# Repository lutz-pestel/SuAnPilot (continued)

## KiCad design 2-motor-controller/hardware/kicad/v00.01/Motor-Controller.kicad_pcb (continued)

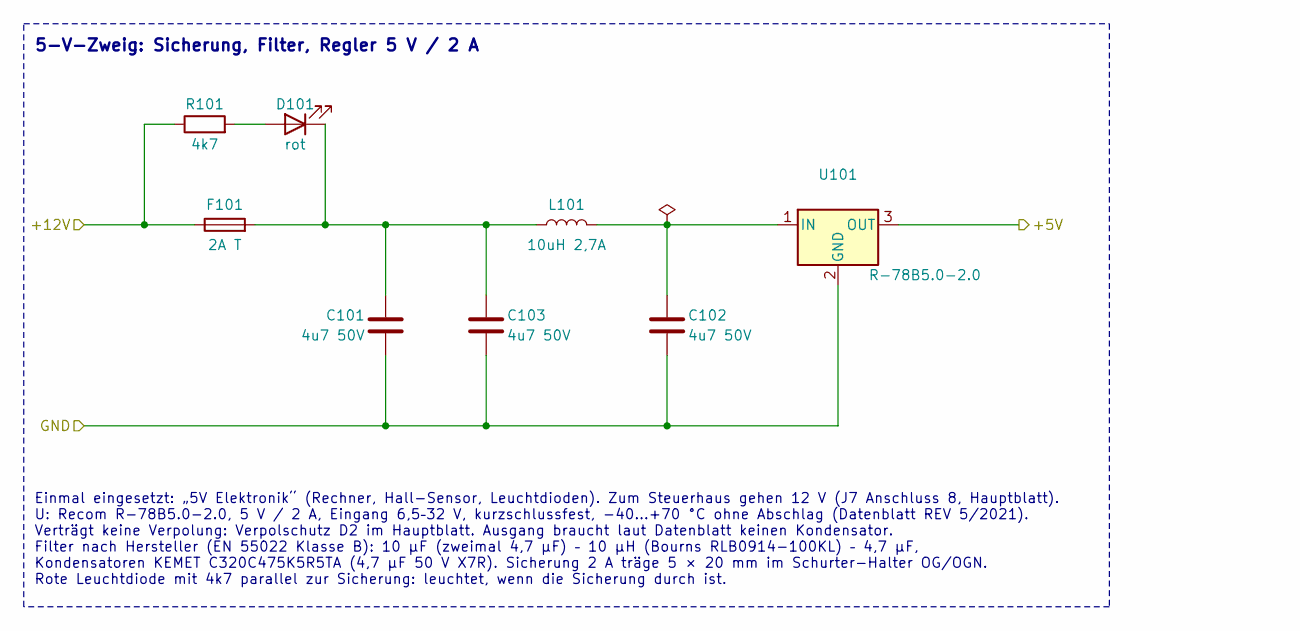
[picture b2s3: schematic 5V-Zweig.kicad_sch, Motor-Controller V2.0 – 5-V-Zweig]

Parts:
C101, C102, C103: 4u7 50V; C_KEMET_C320_L5.1mm_W4.1mm_P2.54mm
D101: rot; LED_Dialight_551_RightAngle
F101: 2A T; Fuseholder_Cylinder-5x20mm_Schurter_0031_8201_Horizontal_Op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
L101: 10uH 2,7A; L_Radial_D10.0mm_P5.00mm_Fastron_07P
R101: 4k7; R_Axial_DIN0207_L6.3mm_D2.5mm_P10.16mm_Horizontal
U101: R-78B5.0-2.0; Converter_DCDC_RECOM_R-78B-2.0_THT

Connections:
+5V: U101.3 (OUT); also elsewhere on the board
+12V: F101.1, R101.1; also elsewhere on the board
GND: C101.2, C102.2, C103.2, U101.2 (GND); also elsewhere on the board
unnamed: D101.2 (A), R101.2
unnamed: C101.1, C103.1, D101.1 (K), F101.2, L101.1
unnamed: C102.1, L101.2, U101.1 (IN)

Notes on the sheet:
5-V-Zweig: Sicherung, Filter, Regler 5 V / 2 A
Einmal eingesetzt: „5V Elektronik“ (Rechner, Hall-Sensor, Leuchtdioden). Zum Steuerhaus gehen 12 V (J7 Anschluss 8, Hauptblatt). U: Recom R-78B5.0-2.0, 5 V / 2 A, Eingang 6,5–32 V, kurzschlussfest, −40…+70 °C ohne Abschlag (Datenblatt REV 5/2021). Verträgt keine Verpolung: Verpolschutz D2 im Hauptb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

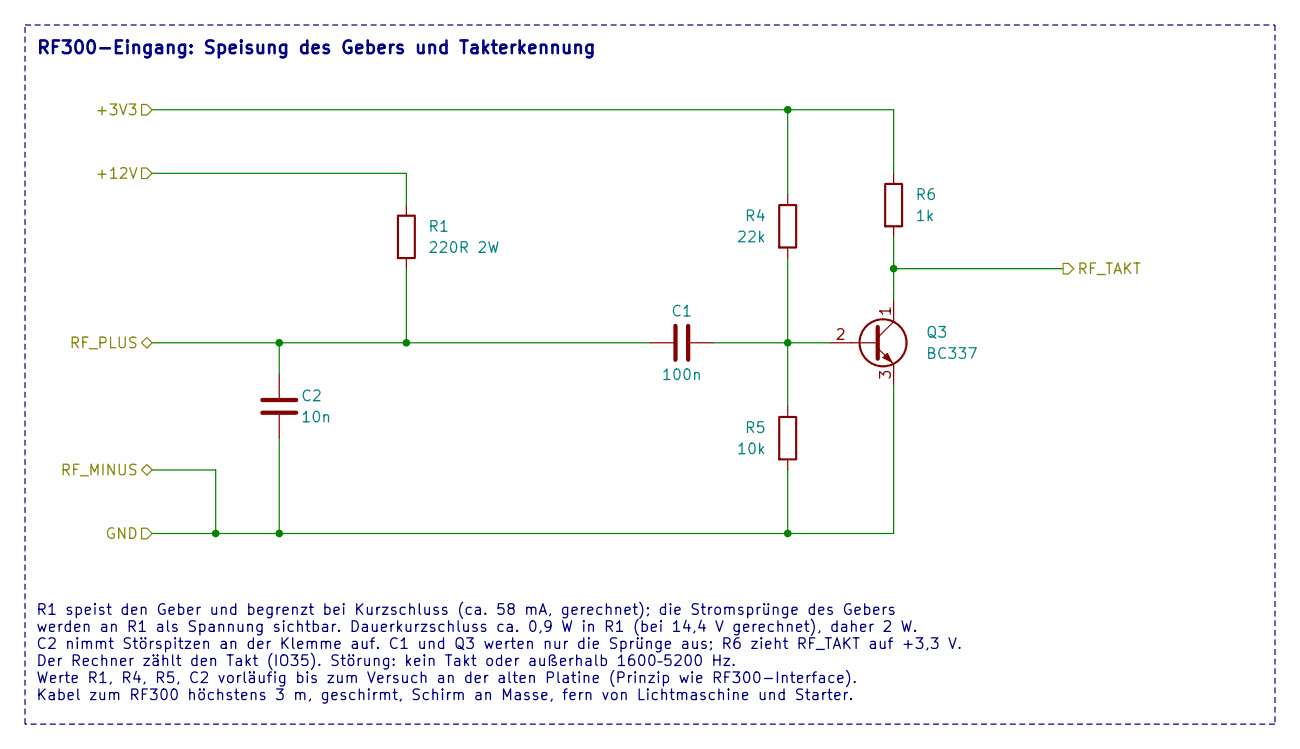
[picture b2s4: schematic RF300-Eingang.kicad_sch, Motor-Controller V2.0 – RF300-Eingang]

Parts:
C1: 100n; C_KEMET_C320_L5.1mm_W4.1mm_P2.54mm
C2: 10n; C_KEMET_C320_L5.1mm_W4.1mm_P2.54mm
Q3: BC337; TO-92_Inline
R1: 220R 2W; R_Axial_DIN0617_L17.0mm_D6.0mm_P20.32mm_Horizontal
R4: 22k; R_Axial_DIN0207_L6.3mm_D2.5mm_P10.16mm_Horizontal
R5: 10k; R_Axial_DIN0207_L6.3mm_D2.5mm_P10.16mm_Horizontal
R6: 1k; R_Axial_DIN0207_L6.3mm_D2.5mm_P10.16mm_Horizontal

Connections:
+3V3: R4.1, R6.1; also elsewhere on the board
+12V: R1.1; also elsewhere on the board
/RF300-Eingang/RF_PLUS: C1.1, C2.1, R1.2; also elsewhere on the board
/RF_TAKT: Q3.1 (C), R6.2; also elsewhere on the board
GND: C2.2, Q3.3 (E), R5.2; also elsewhere on the board
unnamed: C1.2, Q3.2 (B), R4.2, R5.1

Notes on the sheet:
RF300-Eingang: Speisung des Gebers und Takterkennung
R1 speist den Geber und begrenzt bei Kurzschluss (ca. 58 mA, gerechnet); die Stromsprünge des Gebers werden an R1 als Spannung sichtbar. Dauerkurzschluss ca. 0,9 W in R1 (bei 14,4 V gerechnet), daher 2 W. C2 nimmt Störspitzen an der Klemme auf. C1 und Q3 werten nur die Sprünge aus; R6 zieht RF_TAKT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

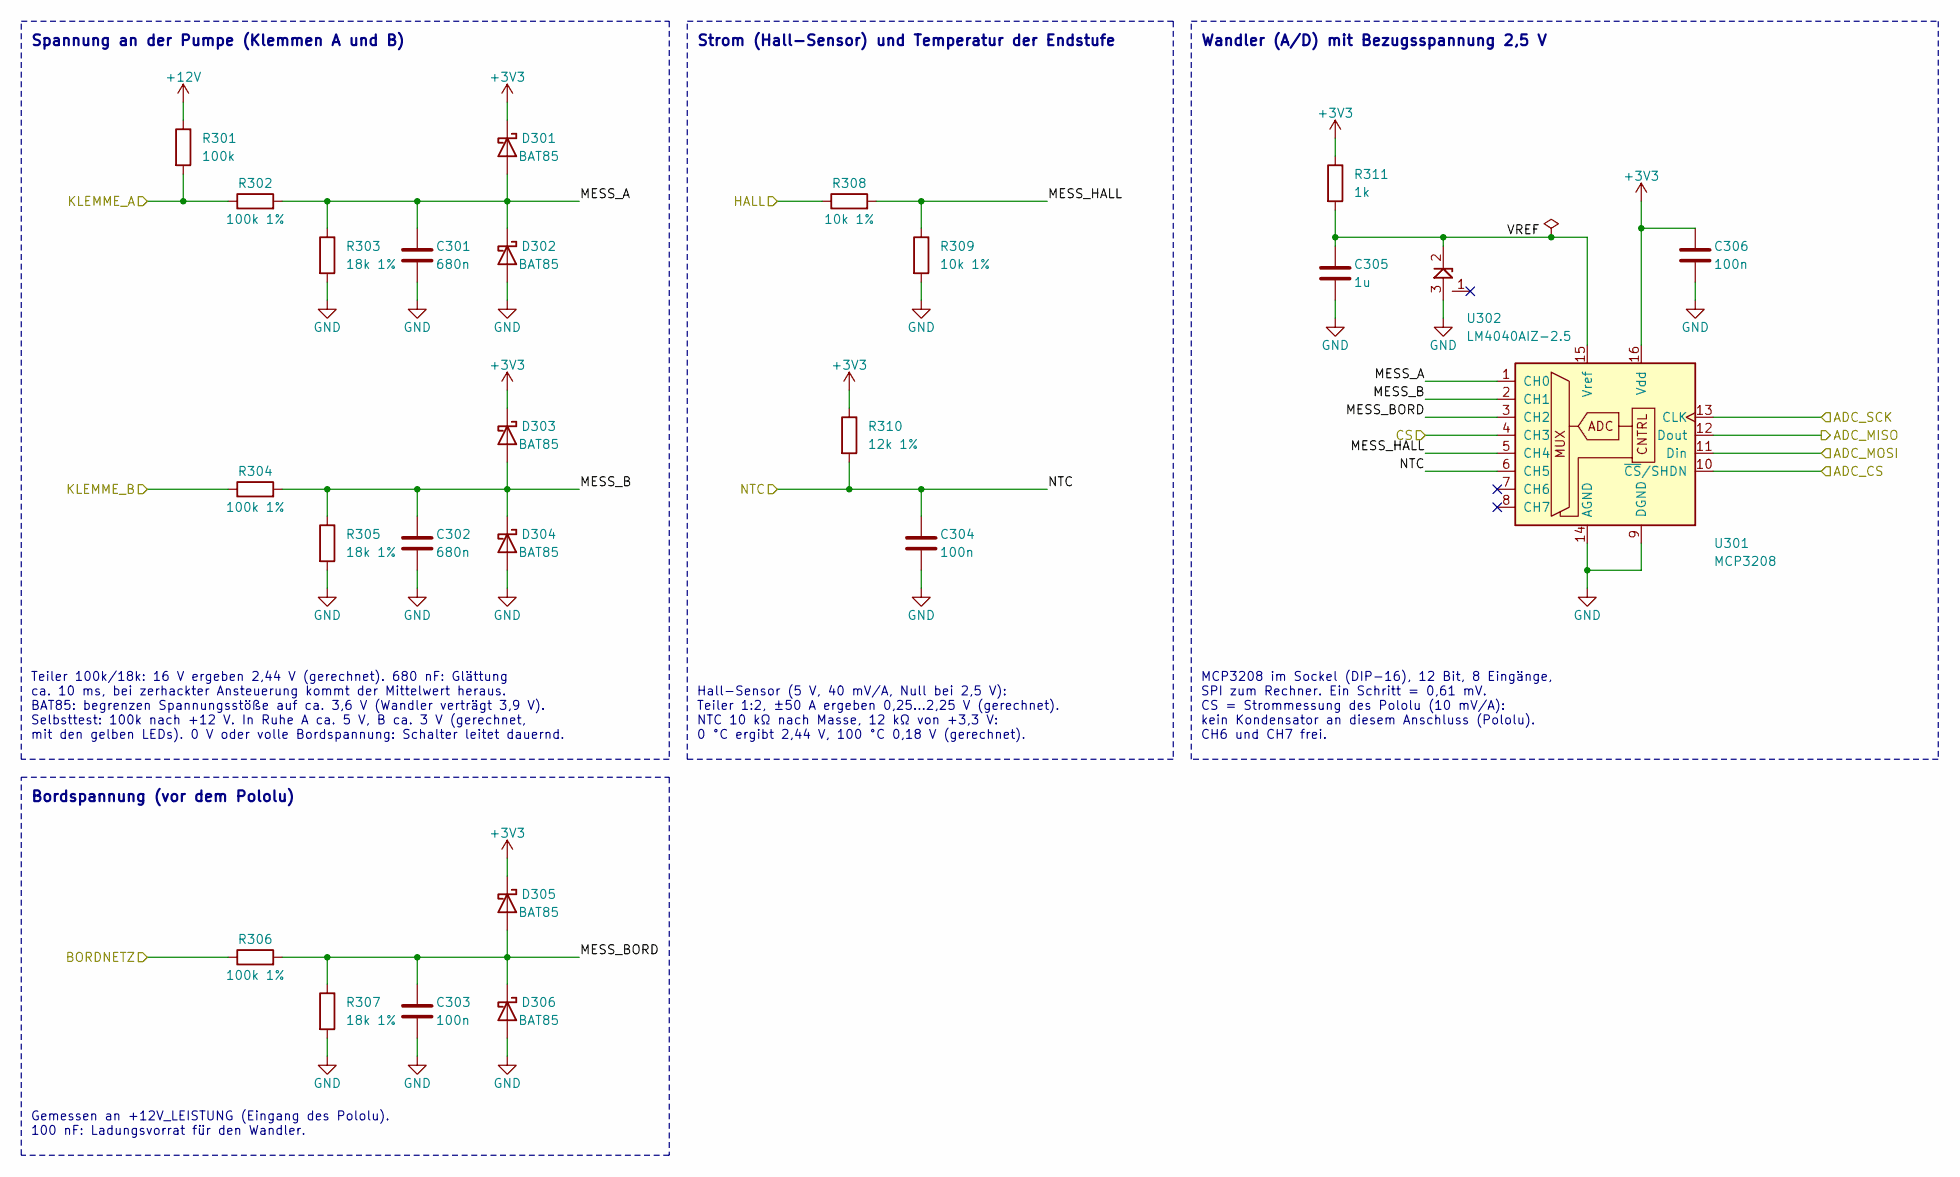
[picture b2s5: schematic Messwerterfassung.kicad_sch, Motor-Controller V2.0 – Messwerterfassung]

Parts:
C301, C302: 680n; C_KEMET_C320_L5.1mm_W4.1mm_P2.54mm
C303, C304, C306: 100n; C_KEMET_C320_L5.1mm_W4.1mm_P2.54mm
C305: 1u; C_Rect_L7.2mm_W4.5mm_P5.00mm_FKS2_FKP2_MKS2_MKP2
D301, D302, D303, D304, D305, D306: BAT85; D_DO-34_SOD68_P7.62mm_Horizontal
R301: 100k; R_Axial_DIN0207_L6.3mm_D2.5mm_P10.16mm_Horizontal
R302, R304, R306: 100k 1%; R_Axial_DIN0207_L6.3mm_D2.5mm_P10.16mm_Horizontal
R303, R305, R307: 18k 1%; R_Axial_DIN0207_L6.3mm_D2.5mm_P10.16mm_Horizontal
R308, R309: 10k 1%; R_Axial_DIN0207_L6.3mm_D2.5mm_P10.16mm_Horizontal
R310: 12k 1%; R_Axial_DIN0207_L6.3mm_D2.5mm_P10.16mm_Horizontal
R311: 1k; R_Axial_DIN0207_L6.3mm_D2.5mm_P10.16mm_Horizontal
U301: MCP3208; DIP-16_W7.62mm_Socket
U302: LM4040AIZ-2.5; TO-92_Inline

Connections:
+3V3: C306.1, D301.1 (K), D303.1 (K), D305.1 (K), R310.1, R311.1, U301.16 (Vdd); also elsewhere on the board
+12V: R301.1; also elsewhere on the board
/+12V_LEISTUNG: R306.1; also elsewhere on the board
/CS: U301.4 (CH3); also elsewhere on the board
/HALL: R308.1; also elsewhere on the board
/KLEMME_A: R301.2, R302.1; also elsewhere on the board
/KLEMME_B: R304.1; also elsewhere on the board
/Messwerterfassung/ADC_CS: U301.10 (~CS/SHDN); also elsewhere on the board
/Messwerterfassung/ADC_MISO: U301.12 (Dout); also elsewhere on the board
/Messwerterfassung/ADC_MOSI: U301.11 (Din); also elsewhere on the board
/Messwerterfassung/ADC_SCK: U301.13 (CLK); also elsewhere on the board
/Messwerterfassung/MESS_A: C301.1, D301.2 (A), D302.1 (K), R302.2, R303.1, U301.1 (CH0)
/Messwerterfassung/MESS_B: C302.1, D303.2 (A), D304.1 (K), R304.2, R305.1, U301.2 (CH1)
/Messwerterfassung/MESS_BORD: C303.1, D305.2 (A), D306.1 (K), R306.2, R307.1, U301.3 (CH2)
/Messwerterfassung/MESS_HALL: R308.2, R309.1, U301.5 (CH4)
/Messwerterfassung/VREF: C305.1, R311.2, U301.15 (Vref), U302.2 (K)
/NTC: C304.1, R310.2, U301.6 (CH5); also elsewhere on the board
GND: C301.2, C302.2, C303.2, C304.2, C305.2, C306.2, D302.2 (A), D304.2 (A), D306.2 (A), R303.2, R305.2, R307.2, R309.2, U301.9 (DGND), U301.14 (AGND), U302.3 (A); also elsewhere on the board

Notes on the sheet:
Wandler (A/D) mit Bezugsspannung 2,5 V
Strom (Hall-Sensor) und Temperatur der Endstufe
MCP3208 im Sockel (DIP-16), 12 Bit, 8 Eingänge, SPI zum Rechner. Ein Schritt = 0,61 mV. CS = Strommessung des Pololu (10 mV/A): kein Kondensator an diesem Anschluss (Pololu). CH6 und CH7 frei.
Teiler 100k/18k: 16 V ergeben 2,44 V (gerechnet). 680 nF: Glättung ca. 10 ms, bei zerhackter Ansteuerung kommt der Mittelwert heraus. BAT85: begrenzen Spannungsstöße auf ca. 3,6 V (Wandler verträgt 3,9 V). Selbsttest: 100k nach +12 V. In Ruhe A ca. 5 V, B ca. 3 V (gerechnet, mit den gelben LEDs). 0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
Spannung an der Pumpe (Klemmen A und B)
Gemessen an +12V_LEISTUNG (Eingang des Pololu). 100 nF: Ladungsvorrat für den Wandler.
Hall-Sensor (5 V, 40 mV/A, Null bei 2,5 V): Teiler 1:2, ±50 A ergeben 0,25…2,25 V (gerechnet). NTC 10 kΩ nach Masse, 12 kΩ von +3,3 V: 0 °C ergibt 2,44 V, 100 °C 0,18 V (gerechnet).
Bordspannung (vor dem Pololu)

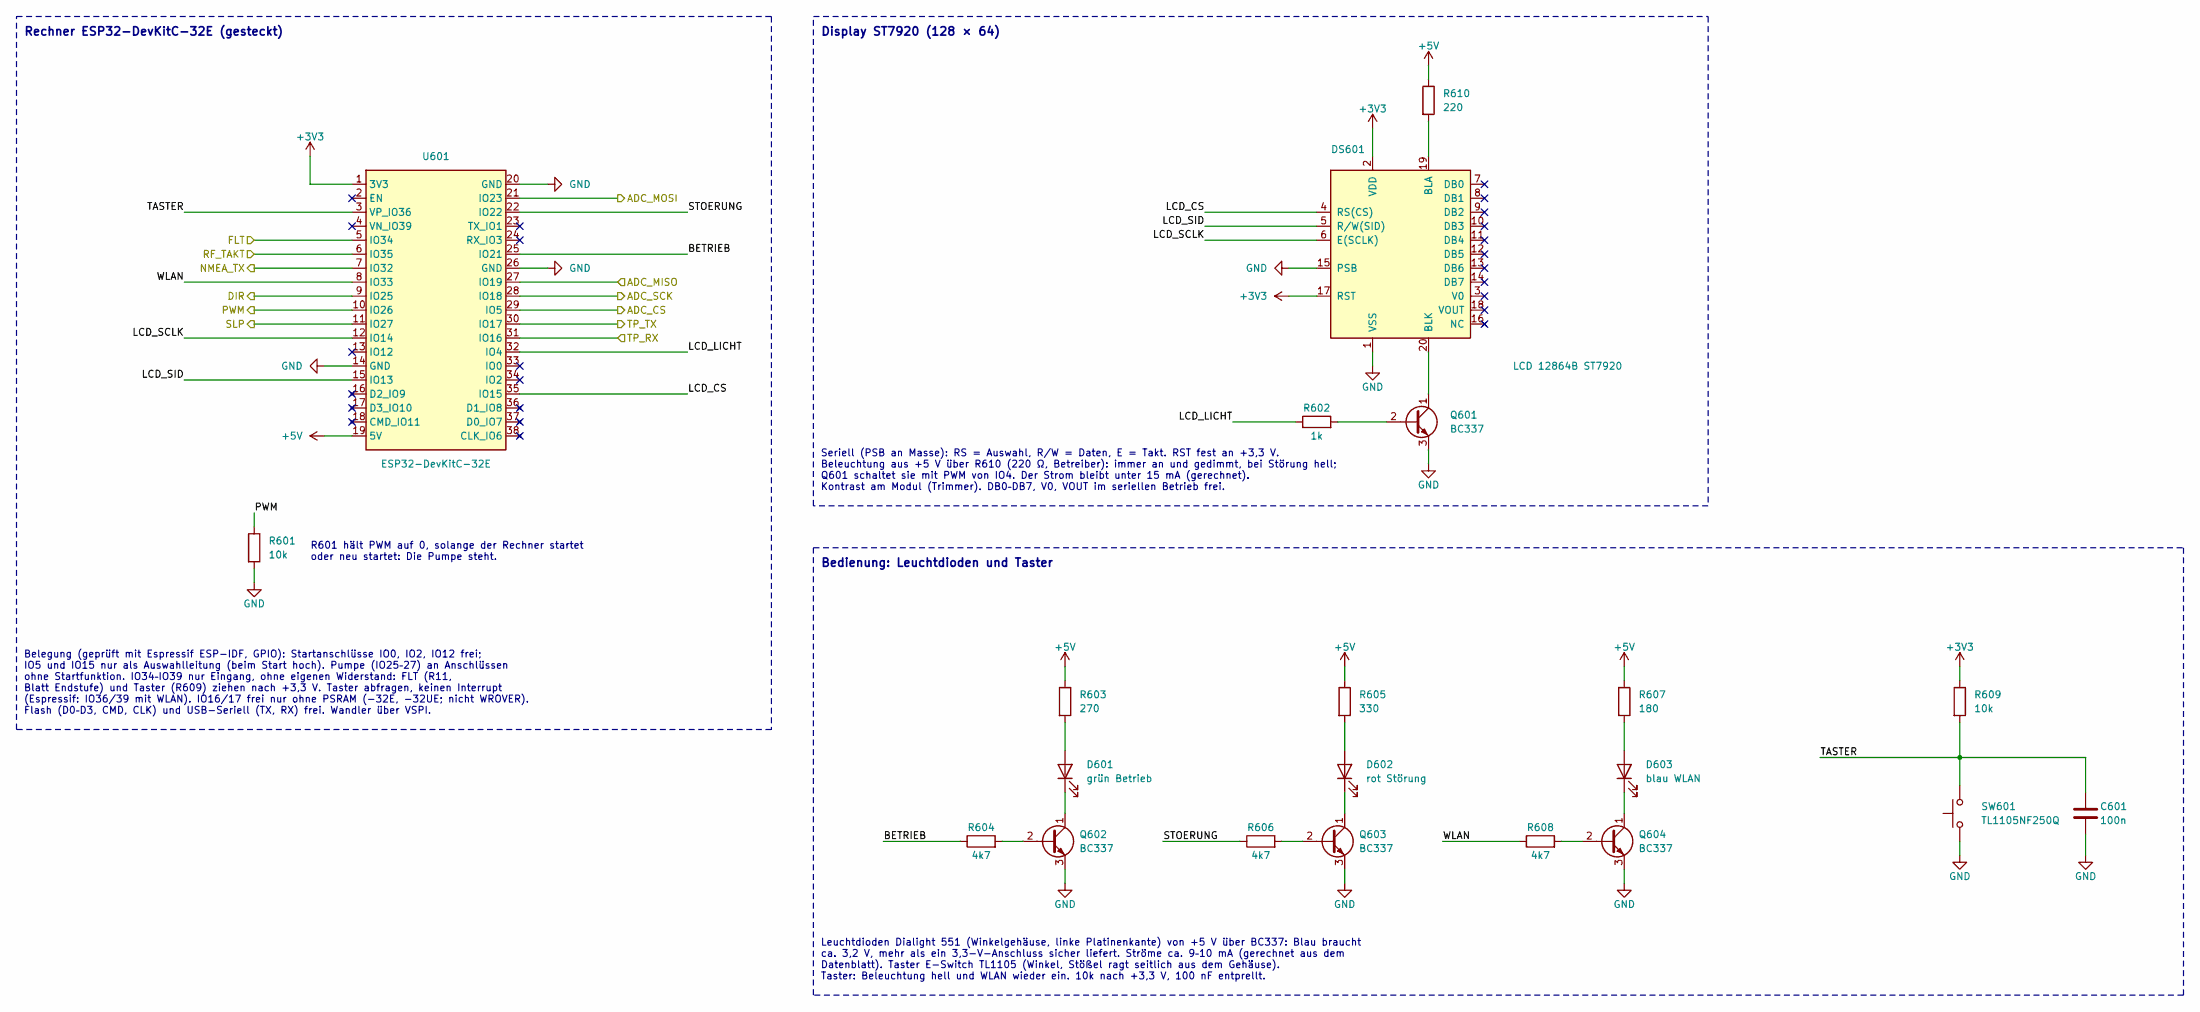
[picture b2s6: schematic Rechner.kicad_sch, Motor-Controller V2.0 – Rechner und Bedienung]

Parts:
C601: 100n; C_KEMET_C320_L5.1mm_W4.1mm_P2.54mm
D601: grün Betrieb; LED_Dialight_551_RightAngle
D602: rot Störung; LED_Dialight_551_RightAngle
D603: blau WLAN; LED_Dialight_551_RightAngle
DS601: LCD 12864B ST7920; LCD_12864B_Socket
Q601, Q602, Q603, Q604: BC337; TO-92_Inline
R601, R609: 10k; R_Axial_DIN0207_L6.3mm_D2.5mm_P10.16mm_Horizontal
R602: 1k; R_Axial_DIN0207_L6.3mm_D2.5mm_P10.16mm_Horizontal
R603: 270; R_Axial_DIN0207_L6.3mm_D2.5mm_P10.16mm_Horizontal
R604, R606, R608: 4k7; R_Axial_DIN0207_L6.3mm_D2.5mm_P10.16mm_Horizontal
R605: 330; R_Axial_DIN0207_L6.3mm_D2.5mm_P10.16mm_Horizontal
R607: 180; R_Axial_DIN0207_L6.3mm_D2.5mm_P10.16mm_Horizontal
R610: 220; R_Axial_DIN0207_L6.3mm_D2.5mm_P10.16mm_Horizontal
SW601: TL1105NF250Q; SW_E-Switch_TL1105_RightAngle
U601: ESP32-DevKitC-32E; ESP32-DevKitC_Socket

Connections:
+3V3: DS601.2 (VDD), DS601.17 (RST), R609.1, U601.1 (3V3); also elsewhere on the board
+5V: R603.1, R605.1, R607.1, R610.1, U601.19 (5V); also elsewhere on the board
/DIR: U601.9 (IO25); also elsewhere on the board
/FLT: U601.5 (IO34); also elsewhere on the board
/Messwerterfassung/ADC_CS: U601.29 (IO5); also elsewhere on the board
/Messwerterfassung/ADC_MISO: U601.27 (IO19); also elsewhere on the board
/Messwerterfassung/ADC_MOSI: U601.21 (IO23); also elsewhere on the board
/Messwerterfassung/ADC_SCK: U601.28 (IO18); also elsewhere on the board
/NMEA_TX: U601.7 (IO32); also elsewhere on the board
/PWM: R601.1, U601.10 (IO26); also elsewhere on the board
/RF_TAKT: U601.6 (IO35); also elsewhere on the board
/Rechner und Bedienung/BETRIEB: R604.1, U601.25 (IO21)
/Rechner und Bedienung/LCD_CS: DS601.4 (RS(CS)), U601.35 (IO15)
/Rechner und Bedienung/LCD_LICHT: R602.1, U601.32 (IO4)
/Rechner und Bedienung/LCD_SCLK: DS601.6 (E(SCLK)), U601.12 (IO14)
/Rechner und Bedienung/LCD_SID: DS601.5 (R/W(SID)), U601.15 (IO13)
/Rechner und Bedienung/STOERUNG: R606.1, U601.22 (IO22)
/Rechner und Bedienung/TASTER: C601.1, R609.2, SW601.2, U601.3 (VP_IO36)
/Rechner und Bedienung/WLAN: R608.1, U601.8 (IO33)
/SLP: U601.11 (IO27); also elsewhere on the board
/TP_RX: U601.31 (IO16); also elsewhere on the board
/TP_TX: U601.30 (IO17); also elsewhere on the board
GND: C601.2, DS601.1 (VSS), DS601.15 (PSB), Q601.3 (E), Q602.3 (E), Q603.3 (E), Q604.3 (E), R601.2, SW601.1, U601.14 (GND), U601.20 (GND), U601.26 (GND); also elsewhere on the board
unnamed: D601.2 (A), R603.2
unnamed: D601.1 (K), Q602.1 (C)
unnamed: D602.2 (A), R605.2
unnamed: D602.1 (K), Q603.1 (C)
unnamed: D603.2 (A), R607.2
unnamed: D603.1 (K), Q604.1 (C)
unnamed: DS601.19 (BLA), R610.2
unnamed: DS601.20 (BLK), Q601.1 (C)
unnamed: Q601.2 (B), R602.2
unnamed: Q602.2 (B), R604.2
unnamed: Q603.2 (B), R606.2
unnamed: Q604.2 (B), R608.2

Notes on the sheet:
Display ST7920 (128 × 64)
Bedienung: Leuchtdioden und Taster
R601 hält PWM auf 0, solange der Rechner startet oder neu startet: Die Pumpe steht.
Seriell (PSB an Masse): RS = Auswahl, R/W = Daten, E = Takt. RST fest an +3,3 V. Beleuchtung aus +5 V über R610 (220 Ω, Betreiber): immer an und gedimmt, bei Störung hell; Q601 schaltet sie mit PWM von IO4. Der Strom bleibt unter 15 mA (gerechnet). Kontrast am Modul (Trimmer). DB0–DB7, V0, VOUT im 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
Belegung (geprüft mit Espressif ESP-IDF, GPIO): Startanschlüsse IO0, IO2, IO12 frei; IO5 und IO15 nur als Auswahlleitung (beim Start hoch). Pumpe (IO25–27) an Anschlüssen ohne Startfunktion. IO34–IO39 nur Eingang, ohne eigenen Widerstand: FLT (R11, Blatt Endstufe) und Taster (R609) ziehen nach +3,3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
Leuchtdioden Dialight 551 (Winkelgehäuse, linke Platinenkante) von +5 V über BC337: Blau braucht ca. 3,2 V, mehr als ein 3,3-V-Anschluss sicher liefert. Ströme ca. 9–10 mA (gerechnet aus dem Datenblatt). Taster E-Switch TL1105 (Winkel, Stößel ragt seitlich aus dem Gehäuse). Taster: Beleuchtung hell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
Rechner ESP32-DevKitC-32E (gesteckt)

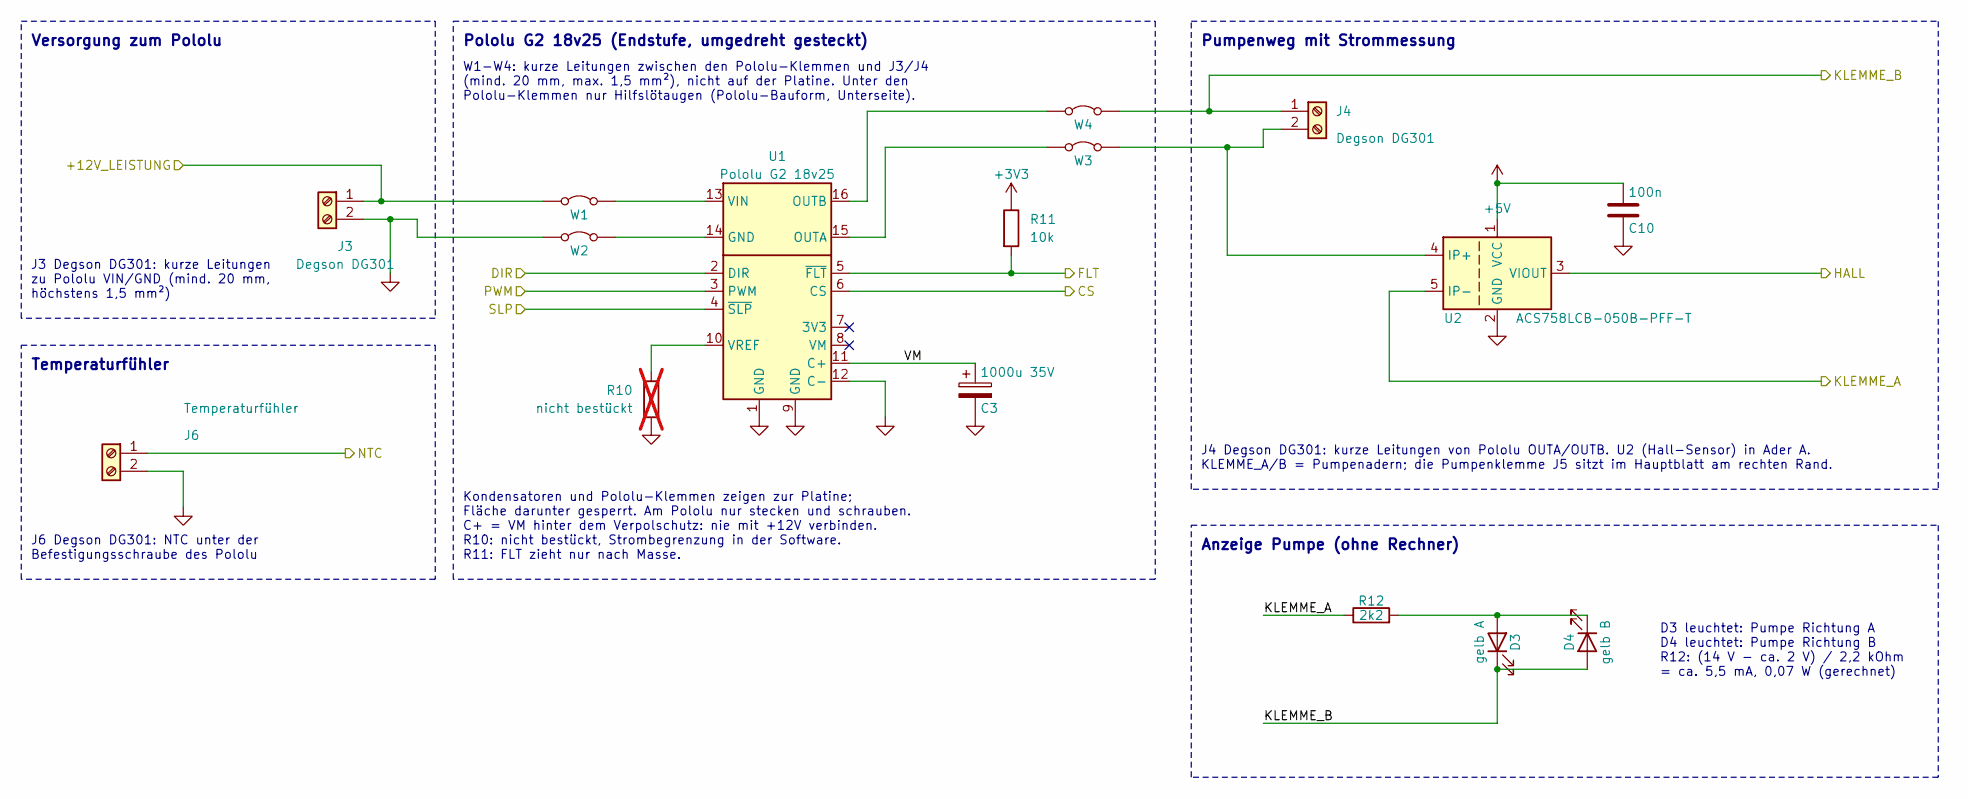
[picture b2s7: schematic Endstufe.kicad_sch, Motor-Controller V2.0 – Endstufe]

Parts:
C3: 1000u 35V; CP_Radial_D12.5mm_P5.00mm
C10: 100n; C_KEMET_C320_L5.1mm_W4.1mm_P2.54mm
D3: gelb A; LED_Dialight_551_RightAngle
D4: gelb B; LED_Dialight_551_RightAngle
J3, J4: Degson DG301; Degson_DG301-5.0-02P
J6: Temperaturfühler; Degson_DG301-5.0-02P
R10: nicht bestückt; R_Axial_DIN0207_L6.3mm_D2.5mm_P10.16mm_Horizontal; not fitted
R11: 10k; R_Axial_DIN0207_L6.3mm_D2.5mm_P10.16mm_Horizontal
R12: 2k2; R_Axial_DIN0207_L6.3mm_D2.5mm_P10.16mm_Horizontal
U1: Pololu G2 18v25; Pololu_G2_18v25_Socket
U2: ACS758LCB-050B-PFF-T; Allegro_CB_PFF
W1, W2, W3, W4: Leitung 20 mm 1,5 mm2

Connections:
+3V3: R11.1; also elsewhere on the board
+5V: C10.1, U2.1 (VCC); also elsewhere on the board
/+12V_LEISTUNG: J3.1, W1.1 (A); also elsewhere on the board
/CS: U1.6 (CS); also elsewhere on the board
/DIR: U1.2 (DIR); also elsewhere on the board
/Endstufe/VM: C3.1, U1.11 (C+)
/FLT: R11.2, U1.5 (~FLT); also elsewhere on the board
/HALL: U2.3 (VIOUT); also elsewhere on the board
/KLEMME_A: R12.1, U2.5 (IP-); also elsewhere on the board
/KLEMME_B: D3.1 (K), D4.2 (A), J4.1, W4.2 (B); also elsewhere on the board
/NTC: J6.1; also elsewhere on the board
/PWM: U1.3 (PWM); also elsewhere on the board
/SLP: U1.4 (~SLP); also elsewhere on the board
GND: C3.2, C10.2, J3.2, J6.2, R10.2, U1.1 (GND), U1.9 (GND), U1.12 (C-), U2.2 (GND), W2.1 (A); also elsewhere on the board
unnamed: D3.2 (A), D4.1 (K), R12.2
unnamed: J4.2, U2.4 (IP+), W3.2 (B)
unnamed: U1.14 (GND), W2.2 (B)
unnamed: U1.15 (OUTA), W3.1 (A)
unnamed: U1.16 (OUTB), W4.1 (A)
unnamed: U1.13 (VIN), W1.2 (B)
unnamed: R10.1, U1.10 (VREF)

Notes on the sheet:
J6 Degson DG301: NTC unter der Befestigungsschraube des Pololu
Pumpenweg mit Strommessung
Versorgung zum Pololu
J4 Degson DG301: kurze Leitungen von Pololu OUTA/OUTB. U2 (Hall-Sensor) in Ader A. KLEMME_A/B = Pumpenadern; die Pumpenklemme J5 sitzt im Hauptblatt am rechten Rand.
W1-W4: kurze Leitungen zwischen den Pololu-Klemmen und J3/J4 (mind. 20 mm, max. 1,5 mm²), nicht auf der Platine. Unter den Pololu-Klemmen nur Hilfslötaugen (Pololu-Bauform, Unterseite).
Temperaturfühler
Anzeige Pumpe (ohne Rechner)
Pololu G2 18v25 (Endstufe, umgedreht gesteckt)
J3 Degson DG301: kurze Leitungen zu Pololu VIN/GND (mind. 20 mm, höchstens 1,5 mm²)
Kondensatoren und Pololu-Klemmen zeigen zur Platine; Fläche darunter gesperrt. Am Pololu nur stecken und schrauben. C+ = VM hinter dem Verpolschutz: nie mit +12V verbinden. R10: nicht bestückt, Strombegrenzung in der Software. R11: FLT zieht nur nach Masse.
D3 leuchtet: Pumpe Richtung A D4 leuchtet: Pumpe Richtung B R12: (14 V - ca. 2 V) / 2,2 kOhm = ca. 5,5 mA, 0,07 W (gerechnet)

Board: 2 copper layers, 85 parts (0 on the bottom side), 64 nets, no tracks yet.

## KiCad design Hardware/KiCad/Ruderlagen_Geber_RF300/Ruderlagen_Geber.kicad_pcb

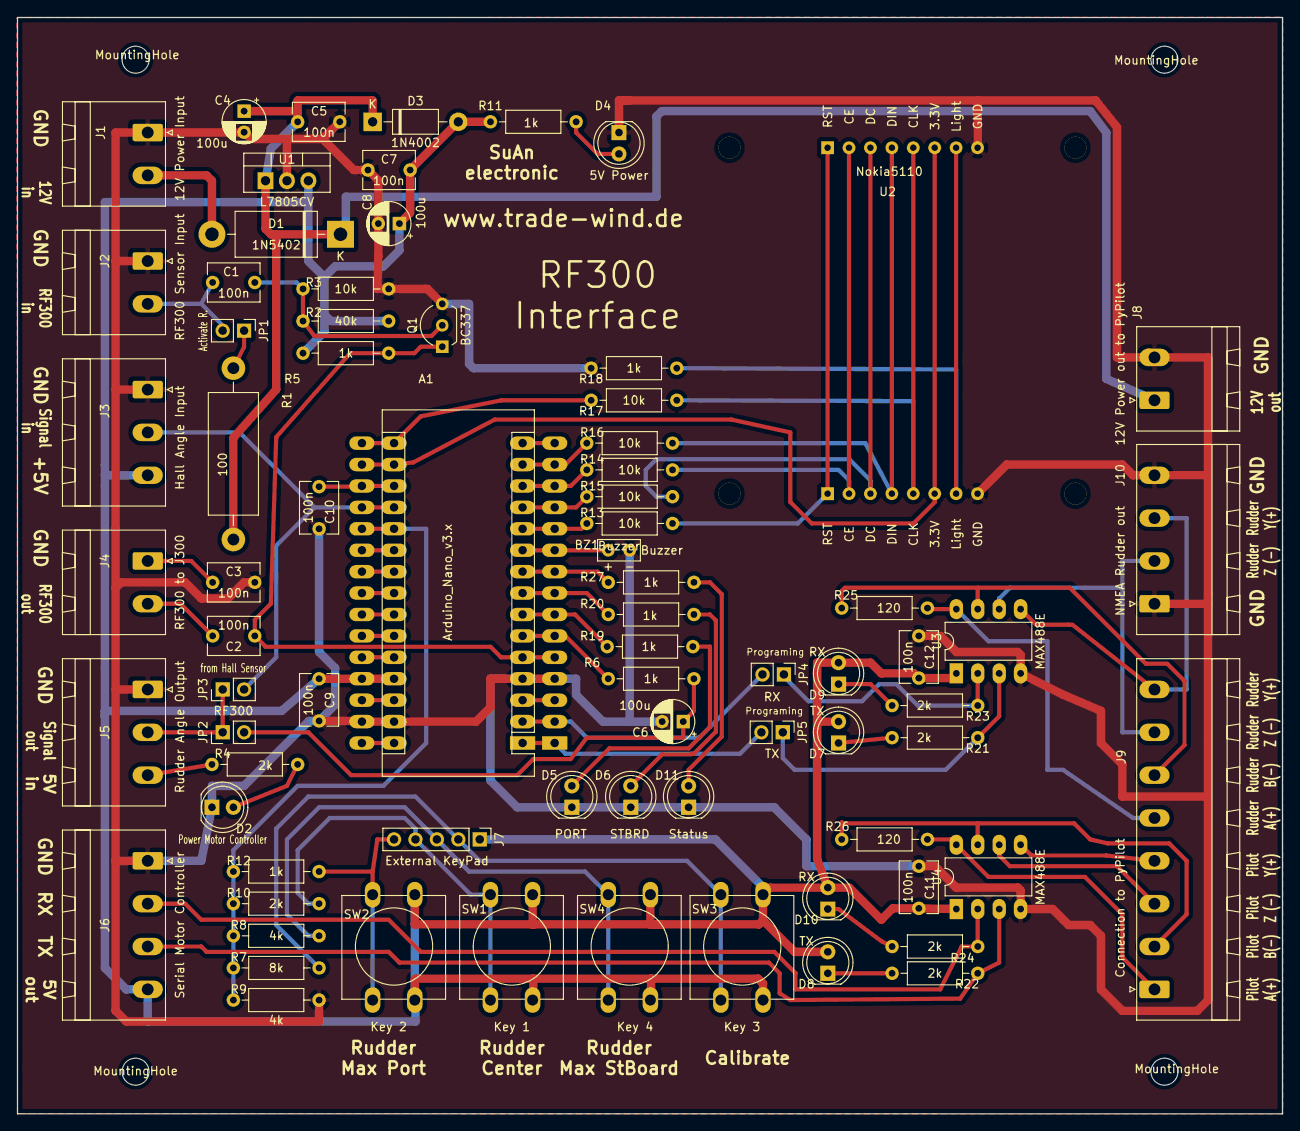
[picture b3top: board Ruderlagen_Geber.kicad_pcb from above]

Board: 2 copper layers, 150.0 x 130.0 mm, 80 parts (0 on the bottom side), 60 nets.

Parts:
A1: Arduino_Nano_v3.x; Arduino_Nano_add_rows
BZ1: Buzzer
C1, C2, C3, C5, C7, C9, C10, C11, C12: 100n; C_Disc_D6.0mm_W4.4mm_P5.00mm
C4, C6, C8: 100u; CP_Radial_D5.0mm_P2.50mm
D1: 1N5402; D_DO-201AD_P15.24mm_Horizontal
D2: Power Motor Controller; LED_D5.0mm
D3: 1N4002; D_DO-41_SOD81_P10.16mm_Horizontal
D4: 5V Power; LED_D5.0mm
D5: PORT; LED_D5.0mm
D6: STBRD; LED_D5.0mm
D7, D8: TX; LED_D5.0mm
D9, D10: RX; LED_D5.0mm
D11: Status; LED_D5.0mm
H1, H2, H3, H4: MountingHole; MountingHole_3.2mm_M3
J1: 12V Power Input; PhoenixContact_MSTBA_2,5_2-G-5,08_1x02_P5.08mm_Horizontal
J2: RF300 Sensor Input; PhoenixContact_MSTBA_2,5_2-G-5,08_1x02_P5.08mm_Horizontal
J3: Hall Angle Input; PhoenixContact_MSTBA_2,5_3-G-5,08_1x03_P5.08mm_Horizontal
J4: RF300 to J300; PhoenixContact_MSTBA_2,5_2-G-5,08_1x02_P5.08mm_Horizontal
J5: Rudder Angle Output; PhoenixContact_MSTBA_2,5_3-G-5,08_1x03_P5.08mm_Horizontal
J6: Serial Motor Controller; PhoenixContact_MSTBA_2,5_4-G-5,08_1x04_P5.08mm_Horizontal
J7: External KeyPad; PinHeader_1x05_P2.54mm_Vertical
J8: 12V Power out to PyPilot; PhoenixContact_MSTBA_2,5_2-G-5,08_1x02_P5.08mm_Horizontal
J9: Connection to PyPilot; PhoenixContact_MSTBA_2,5_8-G-5,08_1x08_P5.08mm_Horizontal
J10: NMEA Rudder out; PhoenixContact_MSTBA_2,5_4-G-5,08_1x04_P5.08mm_Horizontal
JP1: Activate R.; PinHeader_1x02_P2.54mm_Vertical
JP2: RF300; PinHeader_1x02_P2.54mm_Vertical
JP3: from Hall Sensor; PinHeader_1x02_P2.54mm_Vertical
JP4: RX; PinHeader_1x02_P2.54mm_Vertical
JP5: TX; PinHeader_1x02_P2.54mm_Vertical
Q1: BC337; TO-92L_Inline_Wide
R1: 100; R_Axial_DIN0614_L14.3mm_D5.7mm_P20.32mm_Horizontal
R2: 40k; R_Axial_DIN0207_L6.3mm_D2.5mm_P10.16mm_Horizontal
R3, R13, R14, R15, R16, R17: 10k; R_Axial_DIN0207_L6.3mm_D2.5mm_P10.16mm_Horizontal
R4, R10, R21, R22, R23, R24: 2k; R_Axial_DIN0207_L6.3mm_D2.5mm_P10.16mm_Horizontal
R5, R6, R11, R12, R18, R19, R20, R27: 1k; R_Axial_DIN0207_L6.3mm_D2.5mm_P10.16mm_Horizontal
R7: 8k; R_Axial_DIN0207_L6.3mm_D2.5mm_P10.16mm_Horizontal
R8, R9: 4k; R_Axial_DIN0207_L6.3mm_D2.5mm_P10.16mm_Horizontal
R25, R26: 120; R_Axial_DIN0207_L6.3mm_D2.5mm_P10.16mm_Horizontal
SW1: Key 1; SW_PUSH-12mm
SW2: Key 2; SW_PUSH-12mm
SW3: Key 3; SW_PUSH-12mm
SW4: Key 4; SW_PUSH-12mm
U1: L7805CV; TO-220-3_Vertical
U2: Nokia5110
U3, U4: MAX488E; DIP-8_W7.62mm_LongPads

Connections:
+3V3: A1.17, U2.6
+5V: A1.27, C7.1, C8.1, C9.1, C11.2, C12.2, D3.2, D7.2, D8.2, D9.2, D10.2, J3.3, J6.4, J7.1, R2.2, R5.2, R11.2, SW1.2, SW2.2, SW3.2, SW4.2, U1.3, U3.1, U4.1
+12V: C4.1, C5.1, D1.1, D3.1, J8.1, R1.1, U1.1
/Nokia1: R13.2, U2.1
/Nokia2: R14.2, U2.2
/Nokia3: R15.2, U2.3
/Nokia4: R16.2, U2.4
/Nokia5: R17.2, U2.5
/Nokia7: R18.2, U2.7
Buzzer: A1.10, BZ1.1
CE: A1.13, R14.1
CLK: A1.16, R17.1
DC: A1.12, R15.1
DIN: A1.14, R16.1
GND: A1.4, A1.29, BZ1.2, C3.1, C4.2, C5.2, C6.2, C7.2, C8.2, C9.2, C10.1, C11.1, C12.1, D2.1, D4.1, D5.1, D6.1, D11.1, J1.1, J2.1, J3.1, J5.1, J6.1, J8.2, J10.1, J10.4, Q1.3, R3.1, R9.2, R18.1, U1.2, U2.8, U3.4, U4.4
Hall_Sensor: A1.19, J3.2, JP3.2
KeyPad: A1.20, R7.1, R8.1, R9.1, R10.1, R12.1
MotorControllerRS422_A+: J9.1, R26.1, U4.8
MotorControllerRS422_B-: J9.2, R26.2, U4.7
MotorControllerRS422_Y+: J9.4, U4.5
MotorControllerRS422_Z-: J9.3, U4.6
unnamed: A1.1, JP5.2
unnamed: A1.2, JP4.2
unnamed: A1.18, C10.2
unnamed: C1.1, Q1.2, R2.1, R3.2
unnamed: C2.2, J4.2
unnamed: C3.2, J4.1
unnamed: C6.1, JP2.2, R6.1
unnamed: D1.2, J1.2
unnamed: D2.2, R4.2
unnamed: D4.2, R11.1
unnamed: D5.2, R19.2
unnamed: D6.2, R20.2
unnamed: D7.1, R21.1
unnamed: D8.1, R22.1
unnamed: D9.1, R23.1
unnamed: D10.1, R24.1
unnamed: D11.2, R27.1
unnamed: J5.2, JP2.1, JP3.1
unnamed: J5.3, R4.1
unnamed: J7.2, R7.2, SW3.1
unnamed: J7.3, R8.2, SW4.1
unnamed: J7.4, R10.2, SW1.1
unnamed: J7.5, R12.2, SW2.1
unnamed: JP1.1, R1.2
PortLED: A1.7, R19.1
RF300: C1.2, J2.2, JP1.2
RST: A1.11, R13.1
RXMotorControllerTTL: J6.2, R24.2, U4.2
RXRudderAngleTTL: JP4.1, R23.2, U3.2
RudderAngle(FM): A1.5, C2.1, Q1.1, R5.1
RudderAngleRF300(PWM): A1.6, R6.2
RudderAngleRS422_A+: J9.5, R25.1, U3.8
RudderAngleRS422_B-: J9.6, R25.2, U3.7
RudderAngleRS422_Y+: J9.8, J10.3, U3.5
RudderAngleRS422_Z-: J9.7, J10.2, U3.6
Status: A1.9, R27.2
StbLED: A1.8, R20.1
TXMotorControllerTTL: J6.3, R22.2, U4.3
TXRudderAngleTTL: JP5.1, R21.2, U3.3

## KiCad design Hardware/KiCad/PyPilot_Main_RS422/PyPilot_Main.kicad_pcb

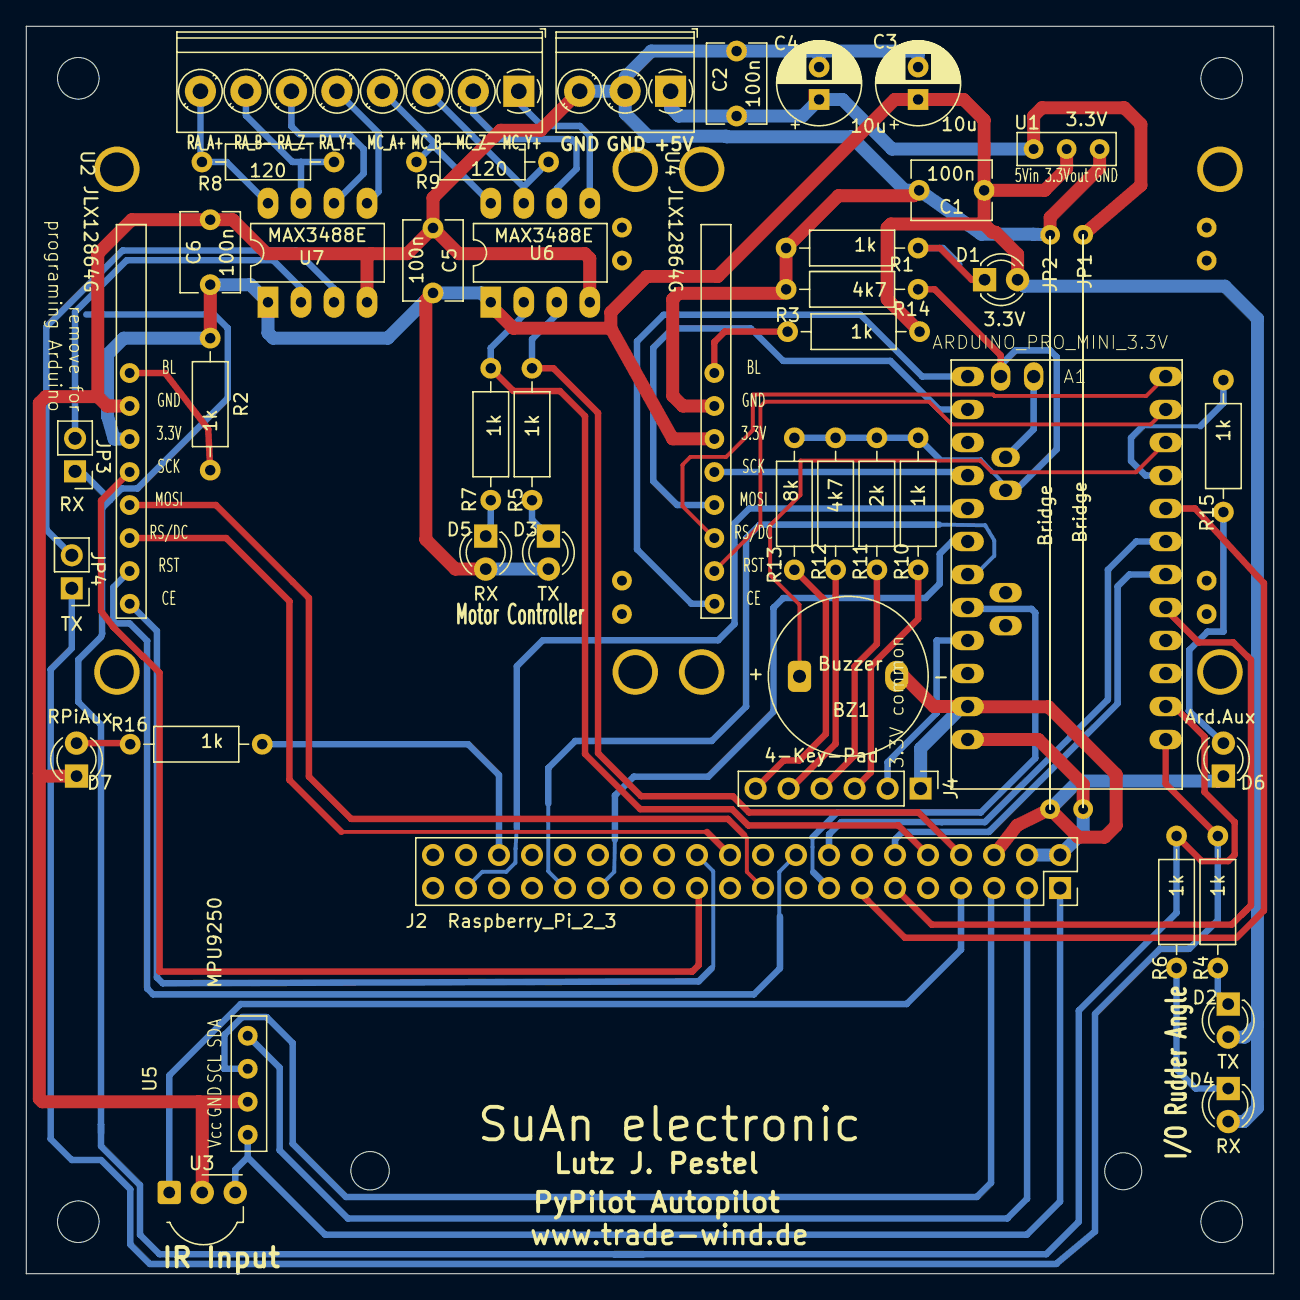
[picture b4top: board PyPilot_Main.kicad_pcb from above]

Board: 2 copper layers, 96.0 x 96.0 mm, 50 parts (0 on the bottom side), 59 nets.

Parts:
A1: ARDUINO_PRO_MINI_3.3V; MODULE_ARDUINO_PRO_MINI_3.3V
BZ1: Buzzer
C1, C2, C5, C6: 100n; C_Disc_D6.0mm_W4.4mm_P5.00mm
C3, C4: 10u; CP_Radial_D6.3mm_P2.50mm
D1: 3.3V; LED_D3.0mm
D2, D3: TX; LED_D3.0mm
D4, D5: RX; LED_D3.0mm
D6: Ard.Aux; LED_D3.0mm
D7: RPiAux; LED_D3.0mm
H1, H2, H3, H4: MountingHole; MountingHole_3.2mm_M3
J1: 5V Power; TerminalBlock_Phoenix_PT-1,5-3-3.5-H_1x03_P3.50mm_Horizontal
J2: Raspberry_Pi_2_3; PinSocket_2x20_P2.54mm_Vertical
J3: Connection to RF300 Interface; TerminalBlock_Phoenix_PT-1,5-8-3.5-H_1x08_P3.50mm_Horizontal
J4: 4-Key-Pad; PinHeader_1x06_P2.54mm_Vertical
JP1, JP2: Bridge; Jumper_Wire_44.169mm
JP3: RX; PinHeader_1x02_P2.54mm_Vertical
JP4: TX; PinHeader_1x02_P2.54mm_Vertical
R1, R2, R3, R4, R5, R6, R7, R10, R15, R16: 1k; R_Axial_DIN0207_L6.3mm_D2.5mm_P10.16mm_Horizontal
R8, R9: 120; R_Axial_DIN0207_L6.3mm_D2.5mm_P10.16mm_Horizontal
R11: 2k; R_Axial_DIN0207_L6.3mm_D2.5mm_P10.16mm_Horizontal
R12, R14: 4k7; R_Axial_DIN0207_L6.3mm_D2.5mm_P10.16mm_Horizontal
R13: 8k; R_Axial_DIN0207_L6.3mm_D2.5mm_P10.16mm_Horizontal
U1: 3.3V; StepDownRegulator5V-3VMS1117_800MA
U2, U4: JLX12864G
U3: TSDP341xx; Vishay_MOLD-3Pin
U5: MPU9250
U6, U7: MAX3488E; DIP-8_W7.62mm_LongPads

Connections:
3V3: A1.21, J4.2
5VBridge: A1.24, J2.2, J2.4, JP1.2
+3V3: C1.1, C3.1, C5.2, C6.2, D1.2, D2.2, D3.2, D4.2, D5.2, R2.1, R3.1, U1.2, U2.7, U4.7, U6.1, U7.1
+5V: C2.1, C4.1, J1.1, JP1.1, U1.1
Arduino_AUX: A1.9, R15.2
Buzzer: A1.10, BZ1.1
DISP1_CE: J2.24, U2.12
DISP1_CLK: J2.23, U2.8
DISP1_DC: J2.22, U2.10
DISP1_DIN(MOSI): J2.19, U2.9
DISP1_RST: J2.18, U2.11
DISP2_CE: A1.13, U4.12
DISP2_CLK: A1.16, U4.8
DISP2_DC: A1.12, U4.10
DISP2_DIN(MOSI): A1.14, U4.9
DISP2_RST: A1.11, U4.11
GND: C1.2, C2.2, C3.2, C4.2, C5.1, C6.1, D7.1, J1.2, J1.3, JP2.2, R1.1, R14.2, U1.3, U2.6, U3.2, U4.6, U5.2, U6.4, U7.4
GND2: A1.23, BZ1.2, D6.1, J2.6, J4.1, JP2.1
IR-Remote: J2.7, U3.1
KB_Auto: A1.5, J2.11
KB_Menue: A1.7, J2.16
KB_Port_1: A1.8, J2.13
KB_Port_10: A1.19, J2.31
KB_Select: A1.6, J2.12
KB_Stb_1: A1.20, J2.15
KB_Stb_10: A1.18, J2.29
KB_Tack: A1.17, J2.37
KeyPad: A1.27, R10.2, R11.2, R12.2, R13.2, R14.1
MPU9250_SCL: J2.5, U5.3
MPU9250_SDA: J2.3, U5.4
MotorControllerRS422_A+: J3.4, R9.1, U6.8
MotorControllerRS422_B-: J3.3, R9.2, U6.7
MotorControllerRS422_Y+: J3.1, U6.5
MotorControllerRS422_Z-: J3.2, U6.6
unnamed: D1.1, R1.2
unnamed: D2.1, R4.1
unnamed: D3.1, R5.1
unnamed: D4.1, R6.1
unnamed: D5.1, R7.1
unnamed: D6.2, R15.1
unnamed: D7.2, R16.1
unnamed: J4.3, R10.1
unnamed: J4.4, R11.1
unnamed: J4.5, R12.1
unnamed: J4.6, R13.1
unnamed: JP3.2, U7.2
unnamed: JP4.2, U7.3
unnamed: R2.2, U2.5
unnamed: R3.2, U4.5
RPI_AUX: J2.36, R16.2
RPi3.3V: J2.1, U3.3, U5.1
RXMotorController3.3V: J2.10, R7.2, U6.2
RXRudderAngle3.3V: A1.2, JP3.1, R6.2
RudderAngleRS422_A+: J3.8, R8.1, U7.8
RudderAngleRS422_B-: J3.7, R8.2, U7.7
RudderAngleRS422_Y+: J3.5, U7.5
RudderAngleRS422_Z-: J3.6, U7.6
TXMotorController3.3V: J2.8, R5.2, U6.3
TXRudderAngle3.3V: A1.1, JP4.1, R4.2
